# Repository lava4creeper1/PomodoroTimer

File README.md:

# Pomodoro Timer

This project is intended to create an arduino controlled timer which implements the pomodoro technique, to help with studying. Achieving this will require electrical, software and mechanical design, the requirements for each of which are listed below.

##  Requirements - Electrical
- The device shall run on an Arduino Nano microcontroller and utilise no more GPIO pins than are available to it
- The device shall contain a seven segment display capable of displaying a countdown
- The device shall contain an LED to visually alert a user when the timer expires
- The device shall contain a buzzer to auditorily alert a user when a timer expires
- The device shall contain a potentiometer capable of controlling the volume of said buzzer
- The device shall contain a vibration device to haptically alert a user when a timer expires
- The device shall contain switches to enable or disable each of these feedback devices; these switches shall be associated with an LED to indicate their state
- The device shall contain a "Begin" button and a "Reset" button to start the timer and stop timer or disable alert, respectively
- The device may, depending on the availability of GPIO pins, be capable of using extra buttons for increased functionality
- The device shall be powered via commonly available household batteries, such as AA or AAA

## Requirements - Software - Incomplete
- TBC

## Requirements - Mechanical - Incomplete
- TBC

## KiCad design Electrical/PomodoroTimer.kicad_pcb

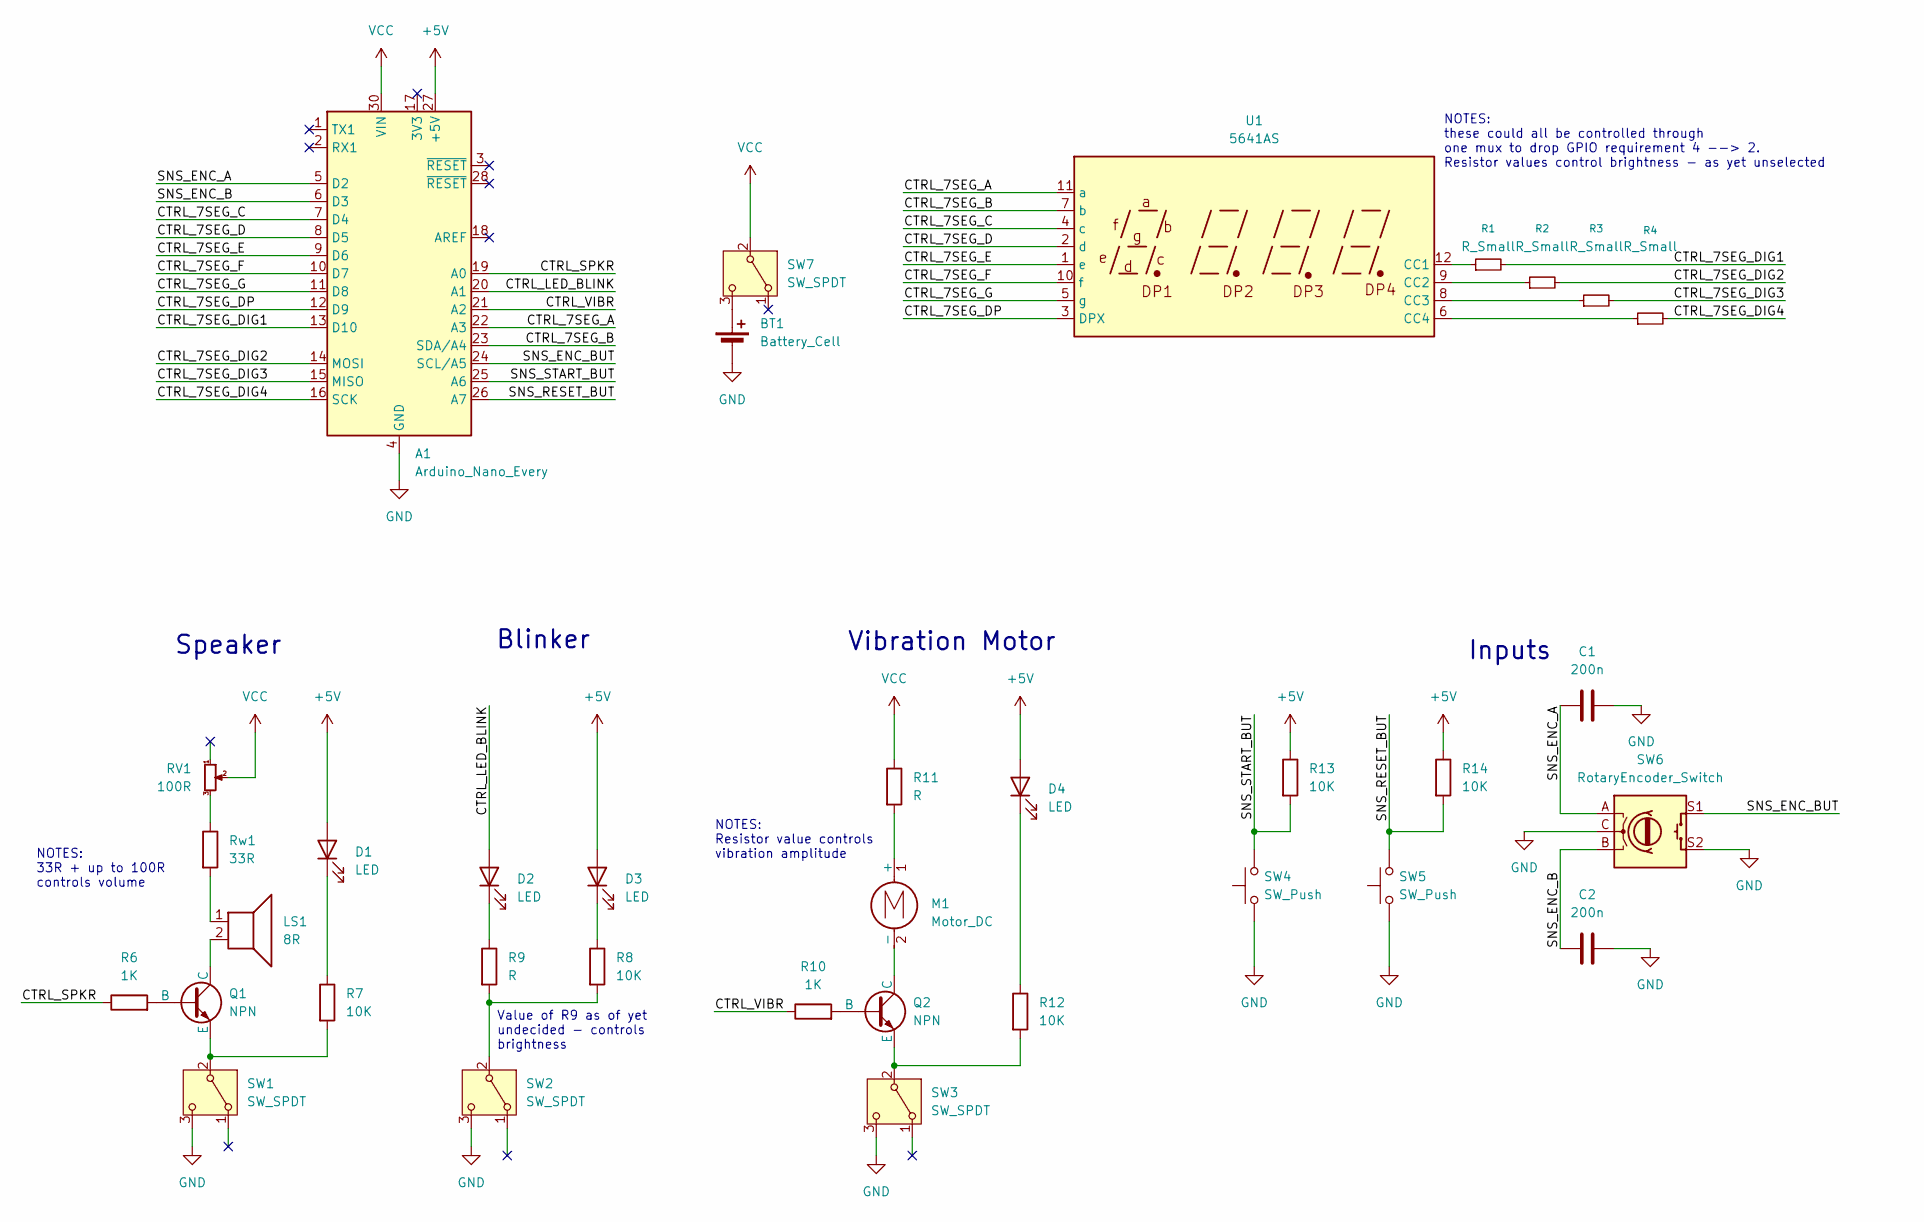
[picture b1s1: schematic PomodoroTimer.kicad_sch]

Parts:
A1: Arduino_Nano_Every; Arduino_Nano
BT1: Battery_Cell; PinHeader_1x02_P2.54mm_Horizontal
C1, C2: 200n; C_Axial_L3.8mm_D2.6mm_P10.00mm_Horizontal
D1, D2, D3, D4: LED; LED_D2.0mm_W4.8mm_H2.5mm_FlatTop
LS1: 8R; PinHeader_1x02_P2.54mm_Horizontal
M1: Motor_DC; PinHeader_1x02_P2.54mm_Horizontal
Q1, Q2: NPN; PinHeader_1x03_P2.54mm_Vertical
R1, R2, R3, R4: R_Small; R_Axial_DIN0207_L6.3mm_D2.5mm_P10.16mm_Horizontal
R6, R10: 1K; R_Axial_DIN0207_L6.3mm_D2.5mm_P10.16mm_Horizontal
R7, R8, R12, R13, R14: 10K; R_Axial_DIN0207_L6.3mm_D2.5mm_P10.16mm_Horizontal
R9, R11: R; R_Axial_DIN0207_L6.3mm_D2.5mm_P10.16mm_Horizontal
RV1: 100R; PinHeader_1x03_P2.54mm_Vertical
Rw1: 33R; R_Axial_DIN0207_L6.3mm_D2.5mm_P10.16mm_Horizontal
SW1, SW2, SW3, SW7: SW_SPDT; PinHeader_1x03_P2.54mm_Vertical
SW4, SW5: SW_Push; SW_SPST_Omron_B3F-40xx
SW6: RotaryEncoder_Switch; RotaryEncoder_Alps_EC11E-Switch_Vertical_H20mm
U1: 5641AS; CA56-12SURKWA

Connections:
+5V: A1.27 (+5V), D1.2 (A), D3.2 (A), D4.2 (A), R13.1, R14.1
/CTRL_7SEG_A: A1.22 (A3), U1.11 (a)
/CTRL_7SEG_B: A1.23 (SDA/A4), U1.7 (b)
/CTRL_7SEG_C: A1.7 (D4), U1.4 (c)
/CTRL_7SEG_D: A1.8 (D5), U1.2 (d)
/CTRL_7SEG_DIG1: A1.13 (D10), R1.2
/CTRL_7SEG_DIG2: A1.14 (MOSI), R2.2
/CTRL_7SEG_DIG3: A1.15 (MISO), R3.2
/CTRL_7SEG_DIG4: A1.16 (SCK), R4.2
/CTRL_7SEG_DP: A1.12 (D9), U1.3 (DPX)
/CTRL_7SEG_E: A1.9 (D6), U1.1 (e)
/CTRL_7SEG_F: A1.10 (D7), U1.10 (f)
/CTRL_7SEG_G: A1.11 (D8), U1.5 (g)
/CTRL_LED_BLINK: A1.20 (A1), D2.2 (A)
/CTRL_SPKR: A1.19 (A0), R6.1
/CTRL_VIBR: A1.21 (A2), R10.1
/SNS_ENC_A: A1.5 (D2), C1.1, SW6.A
/SNS_ENC_B: A1.6 (D3), C2.1, SW6.B
/SNS_ENC_BUT: A1.24 (SCL/A5), SW6.S1
/SNS_RESET_BUT: A1.26 (A7), R14.2, SW5.2
/SNS_START_BUT: A1.25 (A6), R13.2, SW4.2
GND: A1.4 (GND), A1.29 (GND), BT1.2 (-), C1.2, C2.2, SW1.3 (C), SW2.3 (C), SW3.3 (C), SW4.1, SW5.1, SW6.C, SW6.S2
unnamed: BT1.1 (+), SW7.3 (C)
unnamed: D1.1 (K), R7.1
unnamed: D2.1 (K), R9.1
unnamed: D3.1 (K), R8.1
unnamed: D4.1 (K), R12.1
unnamed: LS1.1, Rw1.2
unnamed: M1.1 (+), R11.2
unnamed: M1.2 (-), Q2.1 (C)
unnamed: Q1.2 (B), R6.2
unnamed: LS1.2, Q1.1 (C)
unnamed: Q1.3 (E), R7.2, SW1.2 (B)
unnamed: Q2.2 (B), R10.2
unnamed: Q2.3 (E), R12.2, SW3.2 (B)
unnamed: RV1.3, Rw1.1
unnamed: R8.2, R9.2, SW2.2 (B)
unnamed: R1.1, U1.12 (CC1)
unnamed: R2.1, U1.9 (CC2)
unnamed: R3.1, U1.8 (CC3)
unnamed: R4.1, U1.6 (CC4)
VCC: A1.30 (VIN), R11.1, RV1.2, SW7.2 (B)

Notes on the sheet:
Vibration Motor
Blinker
Inputs
NOTES: 33R + up to 100R controls volume
NOTES: these could all be controlled through one mux to drop GPIO requirement 4 --> 2. Resistor values control brightness - as yet unselected
Speaker
NOTES: Resistor value controls vibration amplitude
Value of R9 as of yet undecided - controls brightness

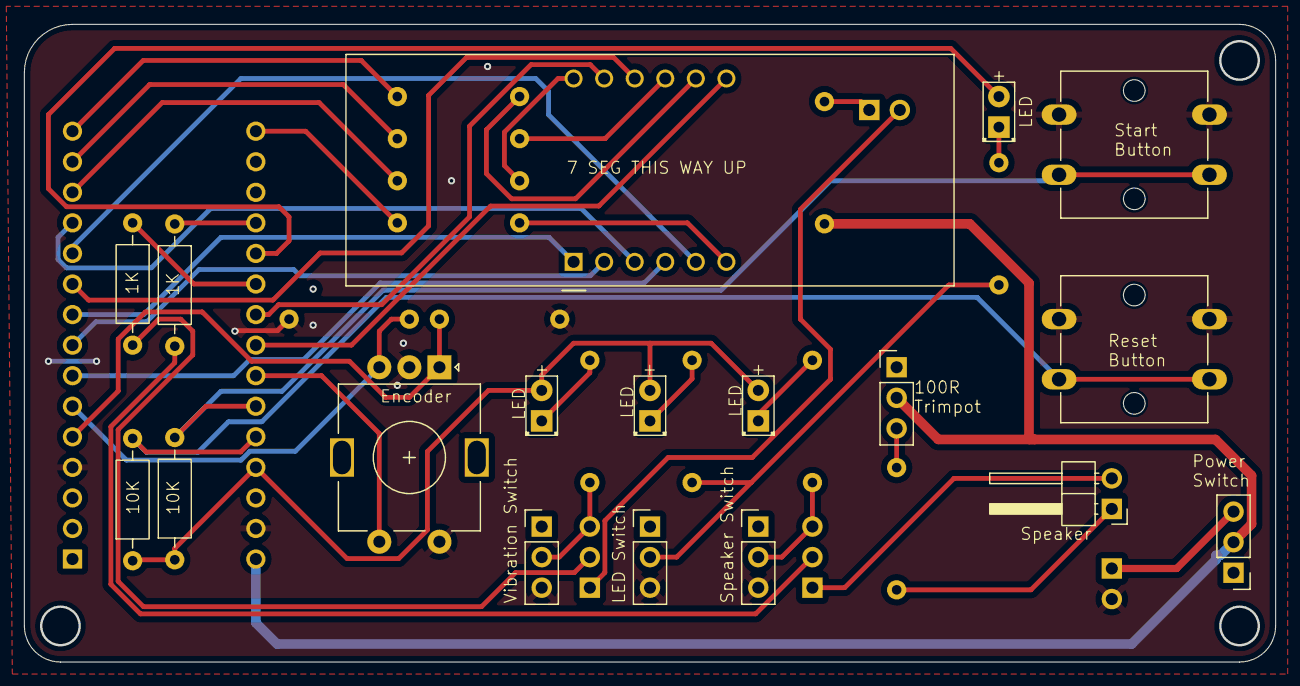
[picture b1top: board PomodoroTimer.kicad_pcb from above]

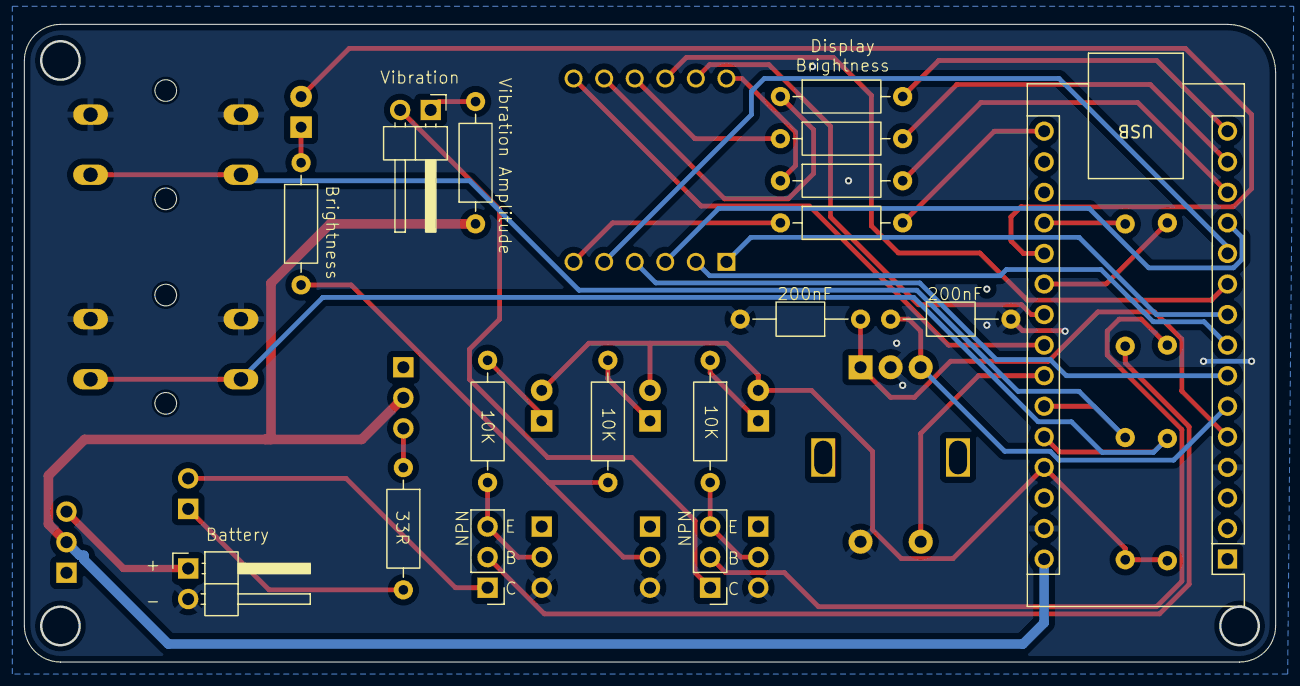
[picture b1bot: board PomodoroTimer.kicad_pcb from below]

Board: 2 copper layers, 103.9 x 52.9 mm, 35 parts (17 on the bottom side), 42 nets.

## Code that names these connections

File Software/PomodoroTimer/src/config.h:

#pragma once

#define SNS_ENCODER_A 2
#define SNS_ENCODER_B 3
#define SNS_ENCODER_BUTTON A5
#define SNS_START_BUTTON A6
#define SNS_RESET_BUTTON A7

#define CTRL_7SEG_A A3
#define CTRL_7SEG_B A4
#define CTRL_7SEG_C 4
#define CTRL_7SEG_D 5
#define CTRL_7SEG_E 6
#define CTRL_7SEG_F 7
#define CTRL_7SEG_G 8
#define CTRL_7SEG_DP 9

#define CTRL_7SEG_DIG_1 10
#define CTRL_7SEG_DIG_2 11
#define CTRL_7SEG_DIG_3 12
#define CTRL_7SEG_DIG_4 13

#define CTRL_SPEAKER A0
#define CTRL_LED_BLINK A1
#define CTRL_VIBRATOR A2

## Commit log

2026-03-16 added readme
2026-03-16 Populated the README file
2026-03-16 Added electrical schematic
2026-03-21 created schematic and pcb design for pomodoro timer
2026-05-25 Added code folder and initialised projectio project
